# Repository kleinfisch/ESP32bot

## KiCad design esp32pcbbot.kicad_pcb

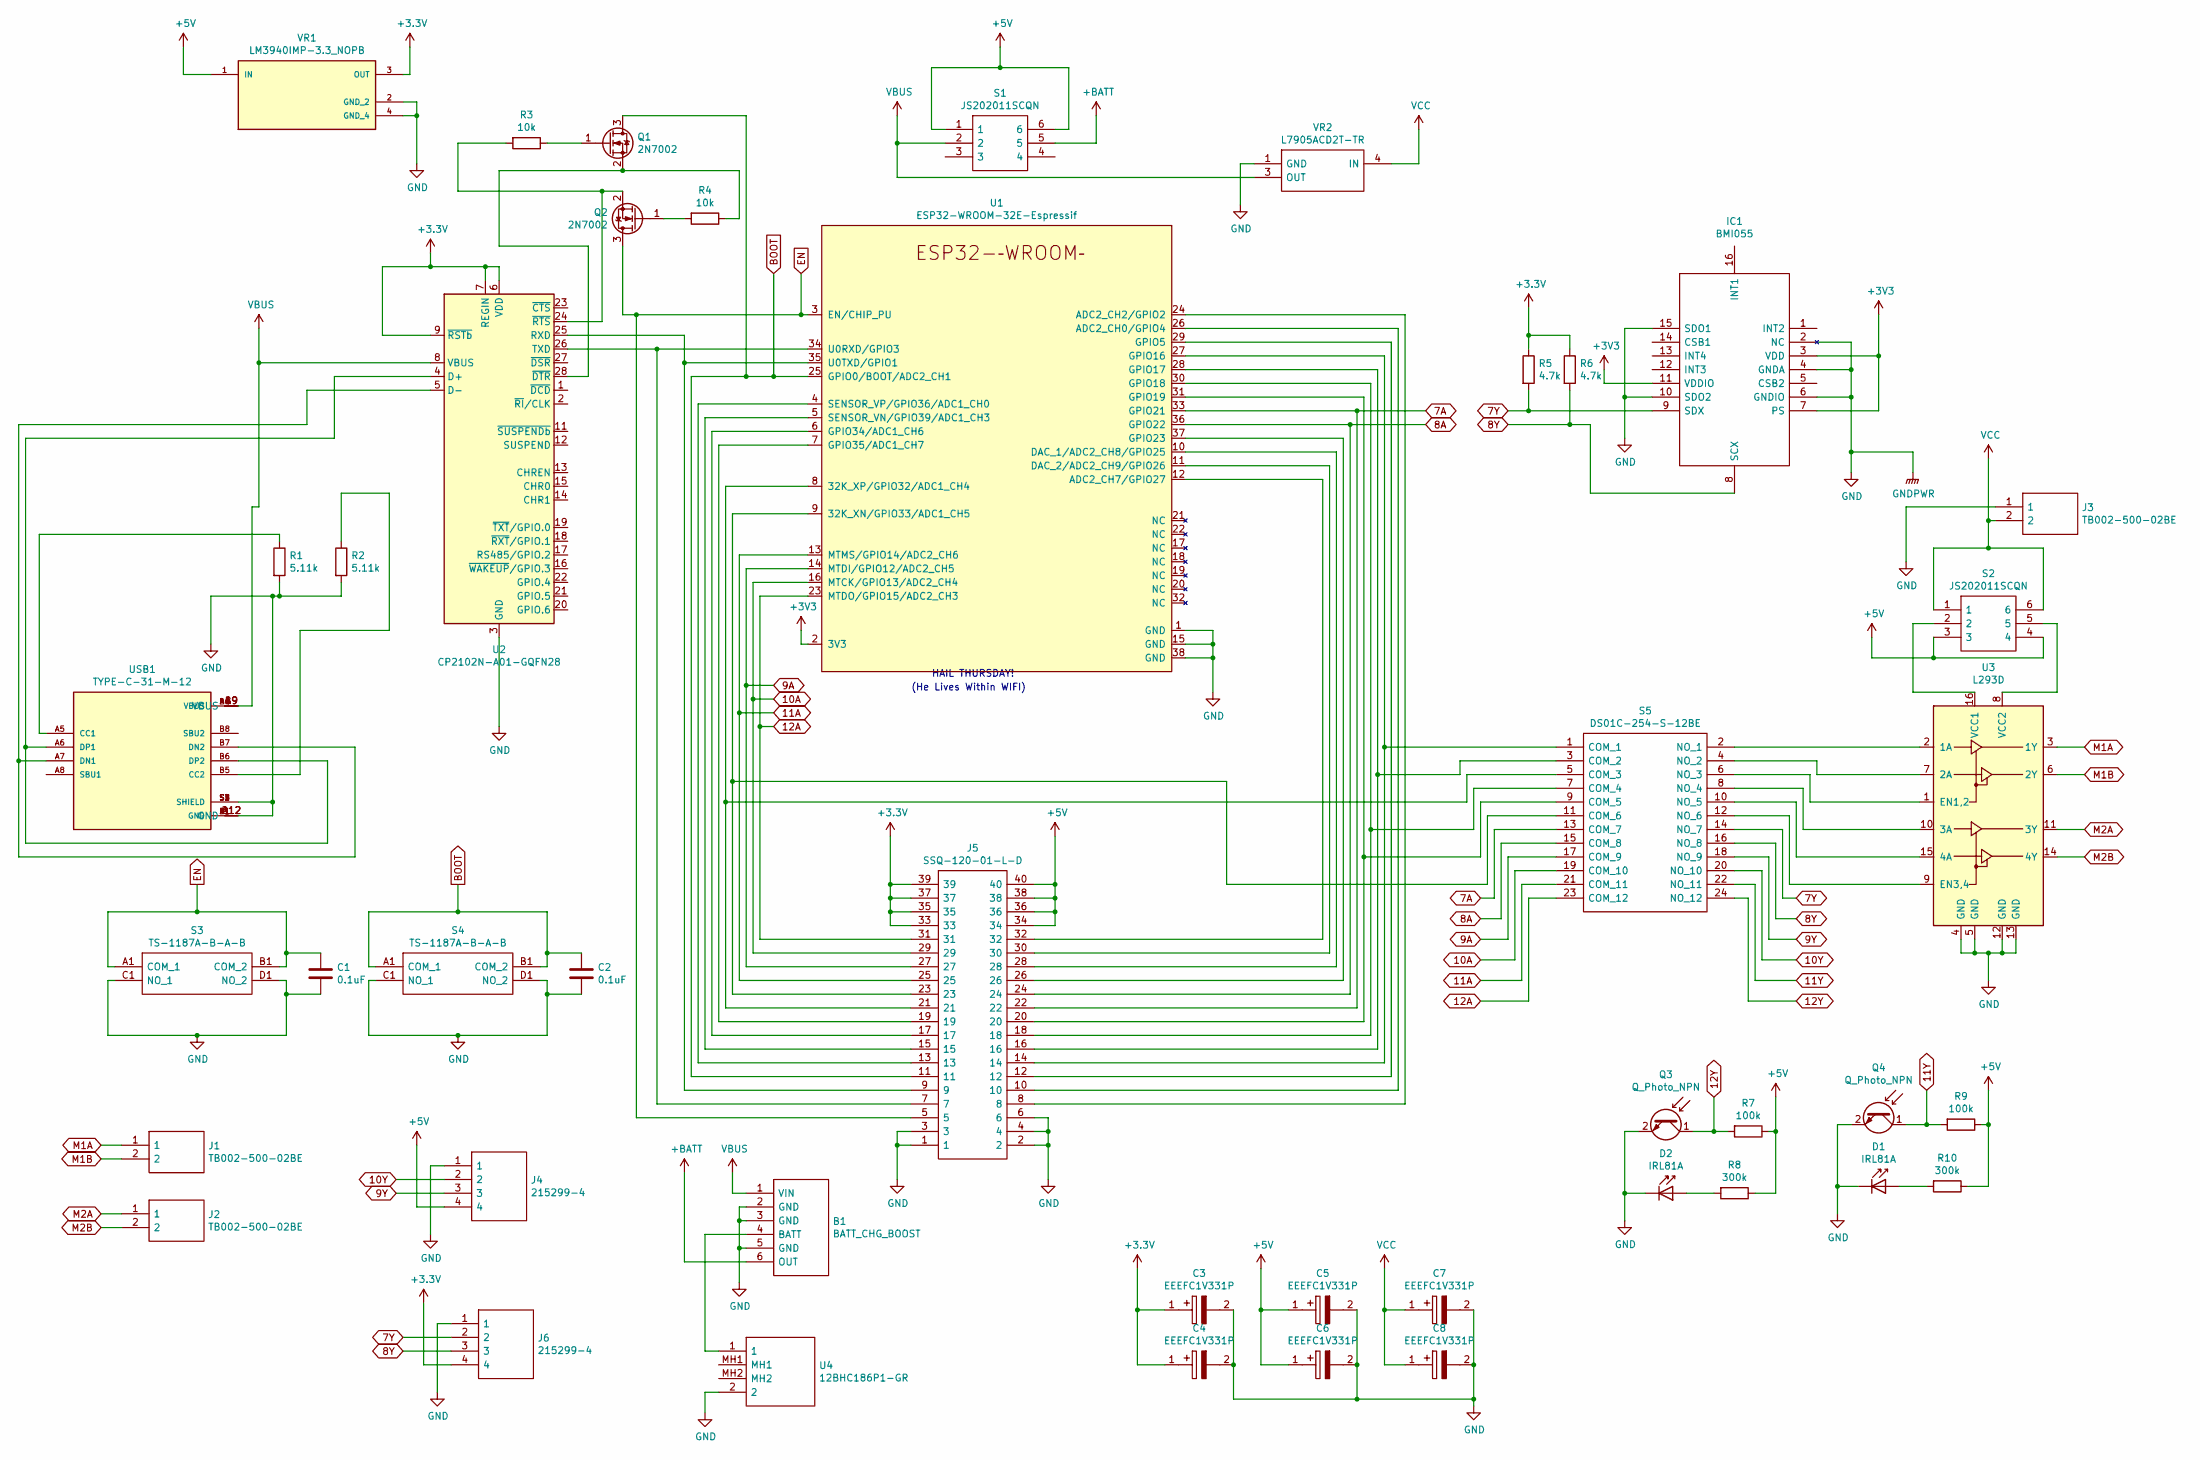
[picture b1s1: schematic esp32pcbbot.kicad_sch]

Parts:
B1: BATT_CHG_BOOST; Manufacturer_Part_Number NaN; Mouser Part Number NaN
C1, C2: 0.1uF; C_0603_1608Metric
C3, C4, C5, C6, C7, C8: EEEFC1V331P; EEEFK1V331P; Manufacturer_Part_Number EEEFC1V331P
D1, D2: IRL81A; LED_D3.0mm
IC1: BMI055; Manufacturer_Part_Number BMI055; Mouser Part Number 262-BMI055
J1, J2, J3: TB002-500-02BE; TB00250002BE; Manufacturer_Part_Number TB002-500-02BE; Mouser Part Number 490-TB002-500-02BE
J4, J6: 215299-4; RHDR4W78P0X254_1X4_1026X252X850P; Manufacturer_Part_Number 215299-4; Mouser Part Number 571-2152994
J5: SSQ-120-01-L-D; SSQ-120-XX-YYY-D; Manufacturer_Part_Number SSQ-120-01-L-D; Mouser Part Number 200-SSQ12001LD
Q1, Q2: 2N7002; SOT-23
Q3, Q4: Q_Photo_NPN; QSD124A4R0
R1, R2: 5.11k; R_0603_1608Metric
R3, R4: 10k; R_0603_1608Metric
R5, R6: 4.7k; R_0603_1608Metric
R7, R9: 100k; R_0603_1608Metric
R8, R10: 300k; R_0603_1608Metric
S1, S2: JS202011SCQN; Manufacturer_Part_Number JS202011SCQN; Mouser Part Number 611-JS202011SCQN
S3, S4: TS-1187A-B-A-B; TS1187ABAB; Manufacturer_Part_Number TS-1187A-B-A-B
S5: DS01C-254-S-12BE; DS01C254S12BE; Manufacturer_Part_Number DS01C-254-S-12BE; Mouser Part Number 490-DS01C-254-S-12BE
U1: ESP32-WROOM-32E-Espressif; ESP32WROOM32EM113EH3200PS3Q0
U2: CP2102N-A01-GQFN28; QFN-28-1EP_5x5mm_P0.5mm_EP3.35x3.35mm
U3: L293D; DIP-16_W7.62mm
U4: 12BHC186P1-GR; 12BHC186P1GR; Mouser Part Number 12BHC186P1-GR
USB1: TYPE-C-31-M-12; USB_C_Receptacle_HRO_TYPE-C-31-M-12; PARTREV A
VR1: LM3940IMP-3.3_NOPB; SOT230P700X180-4N; PARTREV G
VR2: L7905ACD2T-TR; TO254P1542X460-3N; Mouser Part Number 511-L7905ACD2T-TR

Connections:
7A: J5.22, S5.13 (COM_7), U1.33 (GPIO21)
7Y: IC1.9 (SDX), J6.2, R5.2, S5.14 (NO_7)
8A: J5.24, S5.15 (COM_8), U1.36 (GPIO22)
8Y: IC1.8 (SCX), J6.3, R6.2, S5.16 (NO_8)
9A: J5.27, S5.17 (COM_9), U1.14 (MTDI/GPIO12/ADC2_CH5)
9Y: J4.3, S5.18 (NO_9)
10A: J5.29, S5.19 (COM_10), U1.16 (MTCK/GPIO13/ADC2_CH4)
10Y: J4.2, S5.20 (NO_10)
11A: J5.25, S5.21 (COM_11), U1.13 (MTMS/GPIO14/ADC2_CH6)
11Y: Q4.1 (C), R9.2, S5.22 (NO_11)
12A: J5.31, S5.23 (COM_12), U1.23 (MTDO/GPIO15/ADC2_CH3)
12Y: Q3.1 (C), R7.2, S5.24 (NO_12)
+BATT: B1.6 (OUT), S1.5
BOOT: C2.1, J5.11, Q1.3 (D), S4.A1 (COM_1), S4.B1 (COM_2), U1.25 (GPIO0/BOOT/ADC2_CH1)
EN: C1.1, J5.5, Q2.3 (D), S3.A1 (COM_1), S3.B1 (COM_2), U1.3 (EN/CHIP_PU)
GND: B1.2 (GND), B1.3 (GND), B1.5 (GND), C1.2, C2.2, C3.2, C4.2, C5.2, C6.2, C7.2, C8.2, D1.1 (K), D2.1 (K), IC1.2 (NC), IC1.4 (GNDA), IC1.6 (GNDIO), IC1.10 (SDO2), IC1.15 (SDO1), J3.1, J4.1, J5.1, J5.2, J5.3, J5.4, J5.6, J6.1, Q3.2 (E), Q4.2 (E), R1.2, R2.2, S3.C1 (NO_1), S3.D1 (NO_2), S4.C1 (NO_1), S4.D1 (NO_2), U1.1 (GND), U1.15 (GND), U1.38 (GND), U2.3 (GND), U2.29 (GND), U3.4 (GND), U3.5 (GND), U3.12 (GND), U3.13 (GND), U4.2, USB1.A1 (GND), USB1.A12 (GND), USB1.B1 (GND), USB1.B12 (GND), USB1.S1 (SHIELD), USB1.S2 (SHIELD), USB1.S3 (SHIELD), USB1.S4 (SHIELD), VR1.2 (GND_2), VR1.4 (GND_4), VR2.1 (GND)
M1A: J1.1, U3.3 (1Y)
M1B: J1.2, U3.6 (2Y)
M2A: J2.1, U3.11 (3Y)
M2B: J2.2, U3.14 (4Y)
unnamed: B1.4 (BATT), U4.1
unnamed: D1.2 (A), R10.2
unnamed: D2.2 (A), R8.2
unnamed: J5.7, U1.34 (U0RXD/GPIO3), U2.26 (TXD)
unnamed: J5.8, U1.24 (ADC2_CH2/GPIO2)
unnamed: J5.9, U1.35 (U0TXD/GPIO1), U2.25 (RXD)
unnamed: J5.10, U1.26 (ADC2_CH0/GPIO4)
unnamed: J5.12, U1.29 (GPIO5)
unnamed: J5.13, U1.4 (SENSOR_VP/GPIO36/ADC1_CH0)
unnamed: J5.14, S5.1 (COM_1), U1.27 (GPIO16)
unnamed: J5.15, U1.5 (SENSOR_VN/GPIO39/ADC1_CH3)
unnamed: J5.16, S5.3 (COM_2), U1.28 (GPIO17)
unnamed: J5.17, U1.6 (GPIO34/ADC1_CH6)
unnamed: J5.18, S5.7 (COM_4), U1.30 (GPIO18)
unnamed: J5.19, U1.7 (GPIO35/ADC1_CH7)
unnamed: J5.20, S5.9 (COM_5), U1.31 (GPIO19)
unnamed: J5.21, S5.5 (COM_3), U1.8 (32K_XP/GPIO32/ADC1_CH4)
unnamed: J5.23, S5.11 (COM_6), U1.9 (32K_XN/GPIO33/ADC1_CH5)
unnamed: J5.26, U1.37 (GPIO23)
unnamed: J5.28, U1.10 (DAC_1/ADC2_CH8/GPIO25)
unnamed: J5.30, U1.11 (DAC_2/ADC2_CH9/GPIO26)
unnamed: J5.32, U1.12 (ADC2_CH7/GPIO27)
unnamed: Q1.1 (G), R3.1
unnamed: Q1.2 (S), R4.1, U2.28 (~DTR)
unnamed: Q2.1 (G), R4.2
unnamed: Q2.2 (S), R3.2, U2.24 (~RTS)
unnamed: R1.1, USB1.A5 (CC1)
unnamed: R2.1, USB1.B5 (CC2)
unnamed: S2.2, U3.16 (VCC1)
unnamed: S2.5, U3.8 (VCC2)
unnamed: S5.2 (NO_1), U3.2 (1A)
unnamed: S5.4 (NO_2), U3.7 (2A)
unnamed: S5.6 (NO_3), U3.1 (EN1,2)
unnamed: S5.8 (NO_4), U3.10 (3A)
unnamed: S5.10 (NO_5), U3.15 (4A)
unnamed: S5.12 (NO_6), U3.9 (EN3,4)
unnamed: U2.4 (D+), USB1.A6 (DP1), USB1.B6 (DP2)
unnamed: U2.5 (D-), USB1.A7 (DN1), USB1.B7 (DN2)
VBUS: B1.1 (VIN), S1.2, U2.8 (VBUS), USB1.A4 (VBUS), USB1.A9 (VBUS), USB1.B4 (VBUS), USB1.B9 (VBUS), VR2.3 (OUT)
VCC: C7.1, C8.1, J3.2, S2.1, S2.6, VR2.4 (IN)

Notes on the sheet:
(He Lives Within WIFI)
HAIL THURSDAY!

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
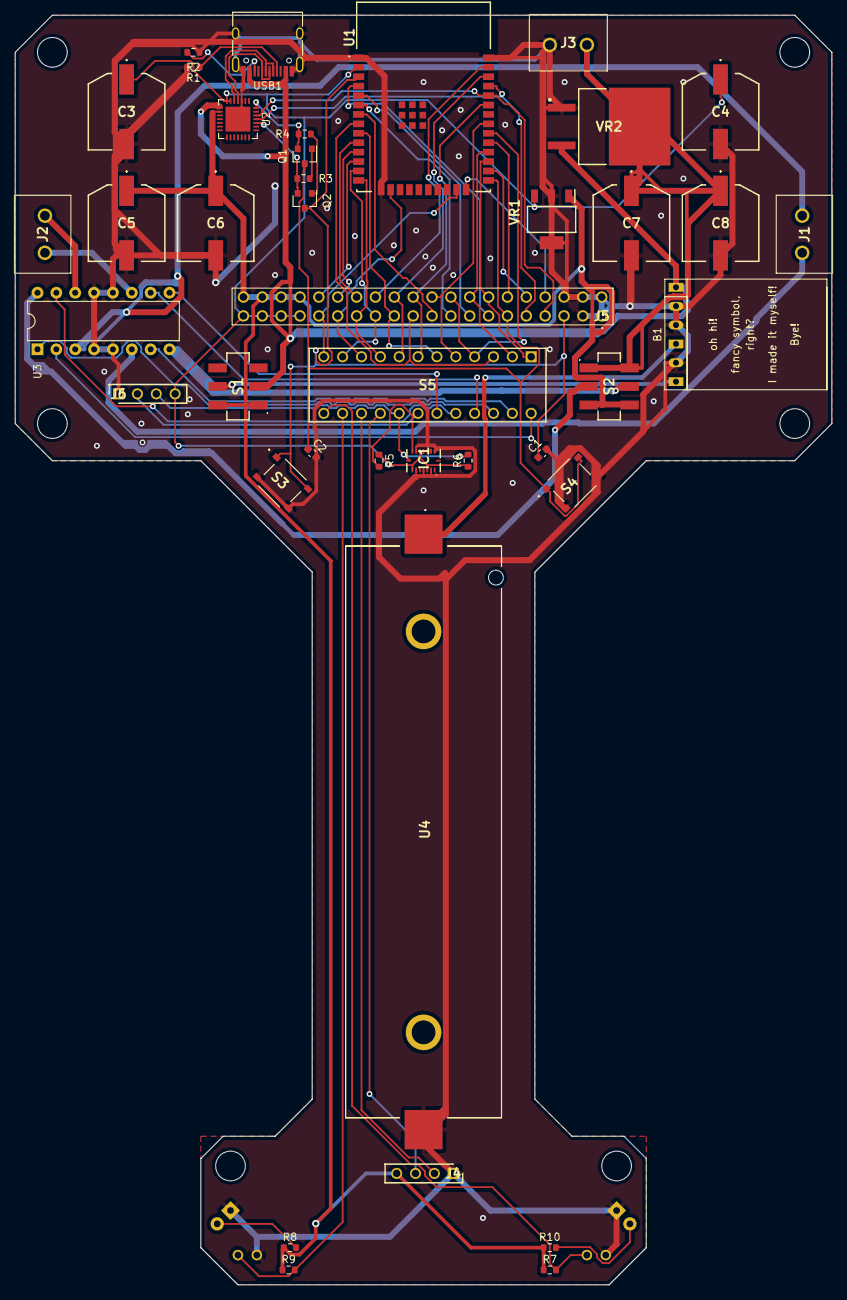
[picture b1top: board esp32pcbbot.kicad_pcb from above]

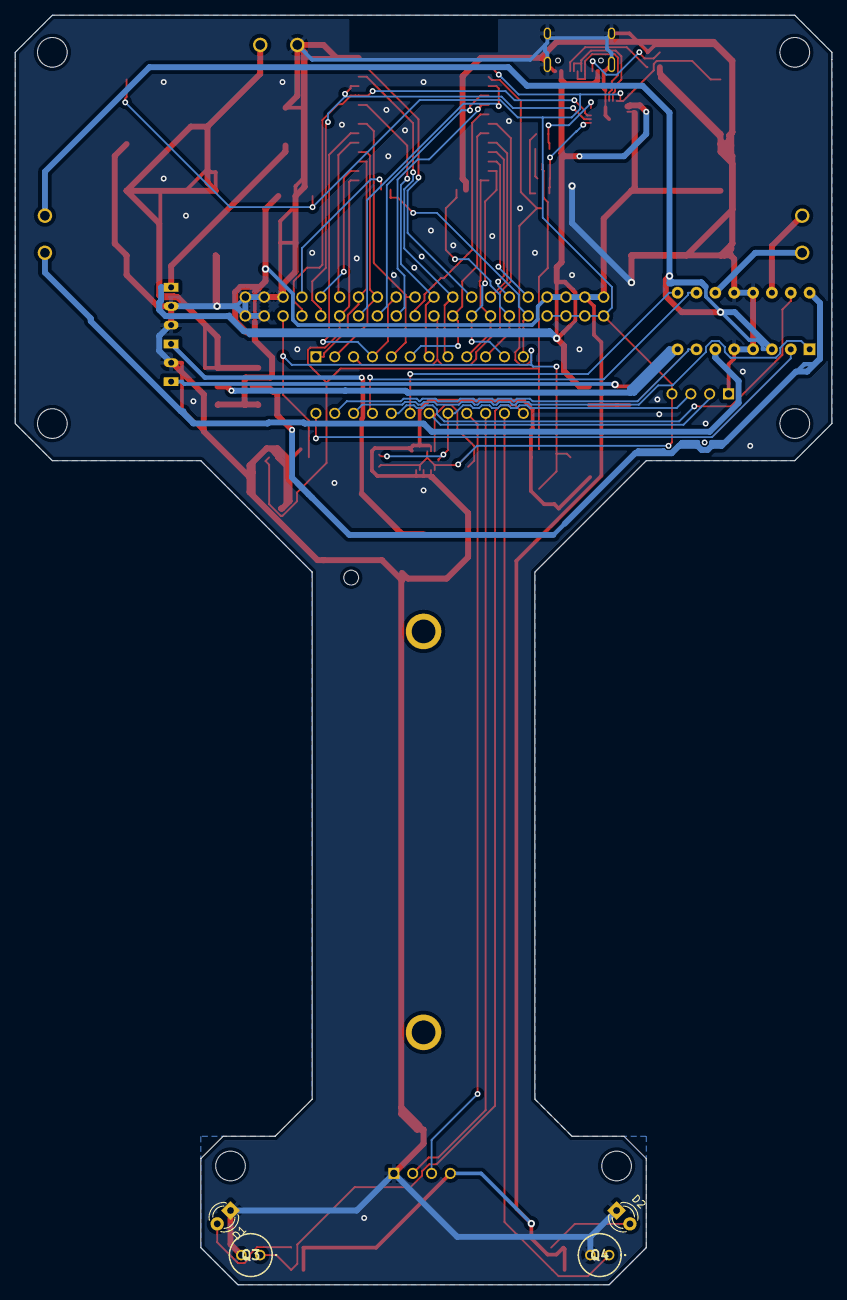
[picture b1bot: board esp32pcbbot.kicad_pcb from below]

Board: 2 copper layers, 110.0 x 171.0 mm, 44 parts (4 on the bottom side), 62 nets.

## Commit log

2022-04-15 Update LICENSE
2022-04-15 esp32 swap for library compatibility
    changed to esp32-waroom-32E to esp32-waroom-32. Maybe legacy lib?
2022-05-09 added accellorometer
    turnturn accellerate added BMI055
2022-05-13 IO, Libload, and TODO
    Added GPIO headers, fixed libload library and #todo list file.
2022-05-14 added boot and en buttons, i2c pullup added, motor power switch added
    modifications to make the design more general purpose.
2022-05-17 generally finished the design
    ayyy schematic is finished
2022-05-17 Update TODO
    have to create pcb still
2022-05-18 i made the pcb
    horay i think its done
2022-05-18 Ran FreeRouting autorouting
    saved as dsn file to be imported to kicad
2022-05-18 Added routed SES file for kicad
    lol i forgot this forgot this the first time
2022-05-18 added routing to KICAD design
    imported SES file
2022-05-19 Added STEP file and renders
    used blue solder mask for one render because it is for wellington : )
2022-05-20 bugfixes and gurber release
    need to put logo on still
2022-05-20 Rearranged and added new spectra DSN
    Hoping for better results and better luck with higher power traces for motors and power lines
2022-05-20 re updated DSN for autorouting
    i did a dumb and fogot to add the actual motor pins
2022-05-20 moved CP2102
    auto rout was glitching so I moved this to make routing easier
2022-05-20 Update esp32pcbbot.dsn
    Oops forgot that last time ^_^
2022-05-20 rearranged AGAIN for auto routing
    wow this is getting really annoying. I hope it works this time.
2022-05-20 tehe **T H I C C T R A C E S**
    MORE CURRENT
2022-05-20 lets see if i can make some MORE THICC TRACES!!!
    i hope this works : )
2022-05-21 ANOTHER attempt at autorouting
    ughhhhh a new layout, one less mounting hole
2022-05-21 grrr more autorouting
    i put the mounting holes back
2022-05-21 MORE AUTOROUTING AAAAAAAAAAAA
    this is very very very very very very very annoying
2022-05-21 A PERFECT ROUT
    YAYYYYYYYYYYYYYYY!!!!!!!!!!!!!!!!!!!!!!!!!!!!!!!!!!!!!!!!!!!!!!!!!!!!!!!!!!!!!!!!
2022-05-21 1 more routing
    THIS IS THE LAST ONE I SWEAR IF I HAVE TO DO 1 MORE ROUTING I AM MAKING ALL 20 ROBOTS ON STRIP BOARD
2022-05-21 It worked
    im done i am so done i do not want to see the word auto rout on a computer screen for the next month. at least im not doing it on perfboard
2022-05-21 IT IS FINISHED!!!!
    I THINK MY DESIGN IS FINALLY FULLY COMPLETE FUNCTIONALLY, logo and aesthetics to be added.
2022-05-22 ...and i sized a voltage regulator incorrectly
    ...goshdangit here we go again autorouting...
2022-05-22 work pls work pls i beg u to finally work
    the ground thingy has been updated
2022-05-22 more autorouting shenanigins
    please work i beg you pleaseworkpleaseworkpleasworkpleasework
2022-05-22 routing more
    please work
2022-05-23 more autorouting
    lets hope this works
2022-05-23 more autorouting
    user error last time, lets hope this one works
2022-05-23 Routing finally worked
    horay
2022-05-23 thiccer traces?
    maybe
2022-05-23 anything thiccer?
    lets hope so
2022-05-23 more autorouting
    horay hora
2022-05-23 more autorouting
    ugh please work i beg you
2022-05-23 try try try again
2022-05-24 finished up the routing stuff
    I think its ready to be ordered!!!
2022-06-03 fixed infuriating board dimensions
    switched from 59 to 60 mm
2022-06-03 dull robot render
    full robot render with motors and stuff
2022-06-03 added full robot render
    fancy lookin
2022-06-27 idek
    mistakes ig
2022-06-27 cp2102 fixes
    wow i screwed up
    who would have thought
2022-06-27 more chaos
2022-07-25 update TODO
    added things to do
2022-07-30 antenna no fill zone setup
2022-07-30 UPDATE TO KICAD V6
    AYYYYYYYYYYYYYY
2022-07-30 fixed i2c breakout, updated TODO
2022-07-30 IDK WHATS HAPPENINGGGGGGG
    GITHUB DID SOMETHING WEIRD
2022-08-18 updated IR sensors
    Switched to an easier to use IR reflectivity module
2022-08-26 Changed as described in TODO
    several changes being made for the next revision
2022-09-07 i did the LED
    glow
2022-09-14 Added LED indicators
    Added to TXT and RXT on CP2102
2022-09-14 fixed git
    hooray
2022-09-22 Update TODO
2022-11-10 cp2102 circuitry layout
    made it more ✨pretty✨
2022-12-13 H bridge and resistors?? idk???
    i dont know wtf i did but it helped
    oh hey i did stuff on the LED indecators
    wait i think i also fixed the power circuitry for the H bridge motor driver
